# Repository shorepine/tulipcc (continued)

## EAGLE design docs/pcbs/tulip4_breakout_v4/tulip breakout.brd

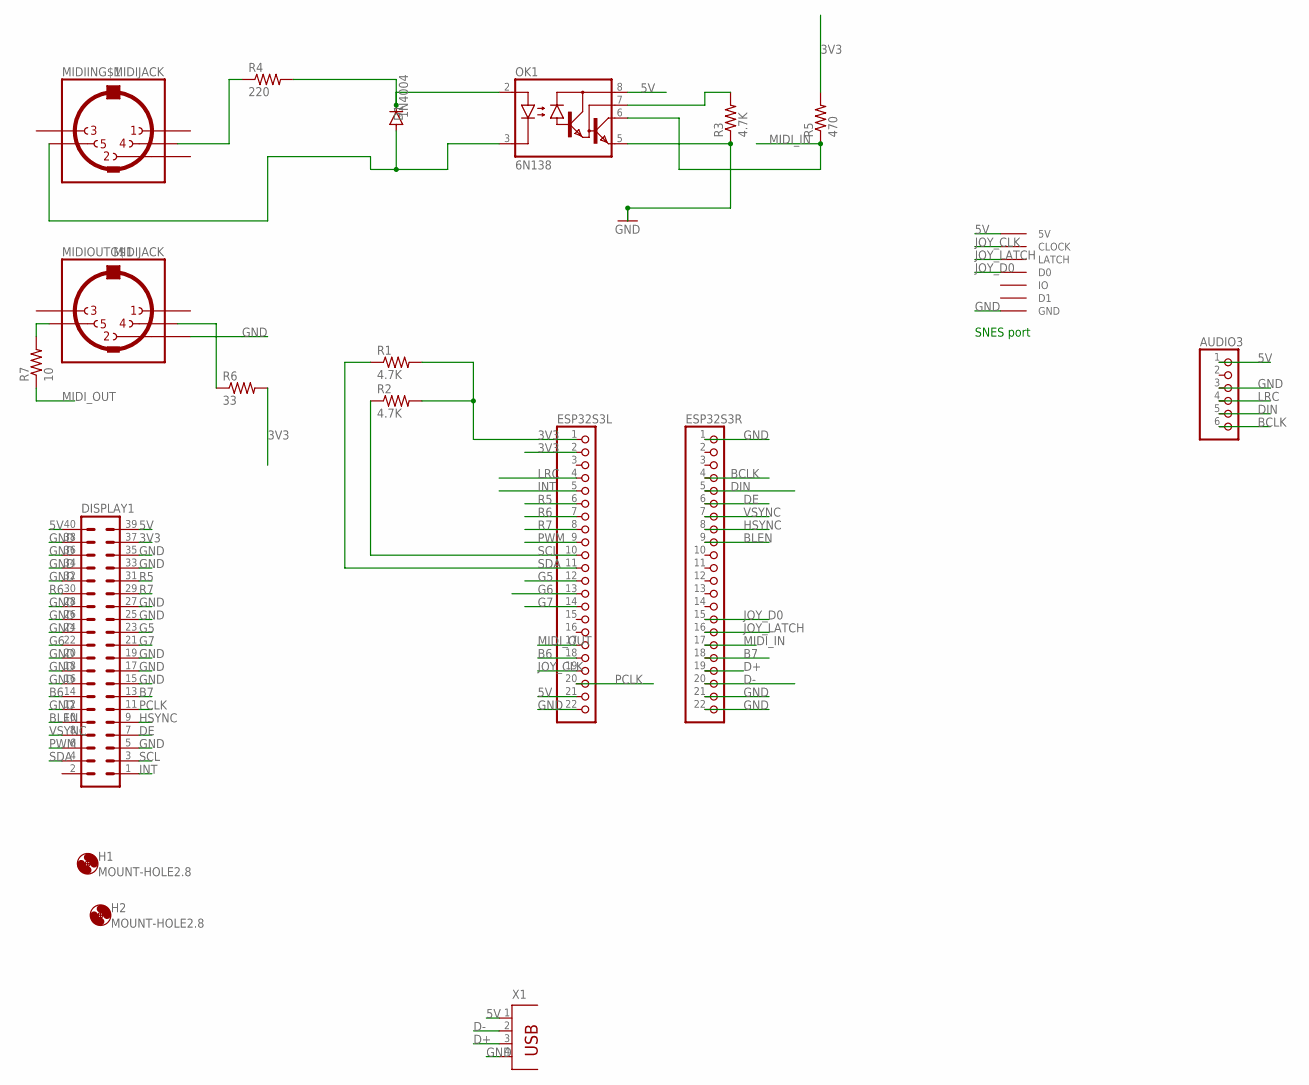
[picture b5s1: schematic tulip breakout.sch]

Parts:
AUDIO3: PINHD-1X6; 1X06
D1: 1N4004; DO41-10
DISPLAY1: MA20-2
ESP32S3L, ESP32S3R: PINHD-1X22; 1X22
H1, H2: MOUNT-HOLE2.8; 2,8
MIDIIN: MIDIJACK; CP-2350
MIDIOUT: MIDIJACK; CP-2350
OK1: 6N138; DIL08
R1, R2, R3: 4.7K; 0207/12
R4: 220; 0207/12
R5: 470; 0207/12
R6: 33; 0207/12
R7: 10; 0207/12
U$2: SNESCONN
X1: PN87520

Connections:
3V3: DISPLAY1.37, ESP32S3L.1, ESP32S3L.2, R1.2, R2.2, R5.2, R6.2
5V: AUDIO3.1, DISPLAY1.39, DISPLAY1.40, ESP32S3L.21, OK1.8 (VCC), U$2.5V, X1.1
B6: DISPLAY1.14, ESP32S3L.18
B7: DISPLAY1.13, ESP32S3R.18
BCLK: AUDIO3.6, ESP32S3R.4
BLEN: DISPLAY1.10, ESP32S3R.9
D+: ESP32S3R.19, X1.3
D-: ESP32S3R.20, X1.2
DE: DISPLAY1.7, ESP32S3R.6
DIN: AUDIO3.5, ESP32S3R.5
G5: DISPLAY1.23, ESP32S3L.12
G6: DISPLAY1.22, ESP32S3L.13
G7: DISPLAY1.21, ESP32S3L.14
GND: AUDIO3.3, DISPLAY1.5, DISPLAY1.12, DISPLAY1.15, DISPLAY1.16, DISPLAY1.17, DISPLAY1.18, DISPLAY1.19, DISPLAY1.20, DISPLAY1.24, DISPLAY1.25, DISPLAY1.26, DISPLAY1.27, DISPLAY1.28, DISPLAY1.32, DISPLAY1.33, DISPLAY1.34, DISPLAY1.35, DISPLAY1.36, DISPLAY1.38, ESP32S3L.22, ESP32S3R.1, ESP32S3R.21, ESP32S3R.22, MIDIOUT.2, OK1.5 (GND), R3.1, U$2.GND, X1.4
HSYNC: DISPLAY1.9, ESP32S3R.8
INT: DISPLAY1.1, ESP32S3L.5
JOY_CLK: ESP32S3L.19, U$2.CLOCK
JOY_D0: ESP32S3R.15, U$2.D0
JOY_LATCH: ESP32S3R.16, U$2.LATCH
LRC: AUDIO3.4, ESP32S3L.4
MIDI_IN: ESP32S3R.17, OK1.6 (VO), R5.1
MIDI_OUT: ESP32S3L.17, R7.1
unnamed: MIDIIN.4, R4.1
unnamed: D1.C, OK1.2 (A), R4.2
unnamed: D1.A, MIDIIN.5, OK1.3 (C)
unnamed: OK1.7 (VB), R3.2
unnamed: MIDIOUT.5, R7.2
unnamed: MIDIOUT.4, R6.1
PCLK: DISPLAY1.11, ESP32S3L.20
PWM: DISPLAY1.6, ESP32S3L.9
R5: DISPLAY1.31, ESP32S3L.6
R6: DISPLAY1.30, ESP32S3L.7
R7: DISPLAY1.29, ESP32S3L.8
SCL: DISPLAY1.3, ESP32S3L.10, R2.1
SDA: DISPLAY1.4, ESP32S3L.11, R1.1
VSYNC: DISPLAY1.8, ESP32S3R.7

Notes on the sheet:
SNES port

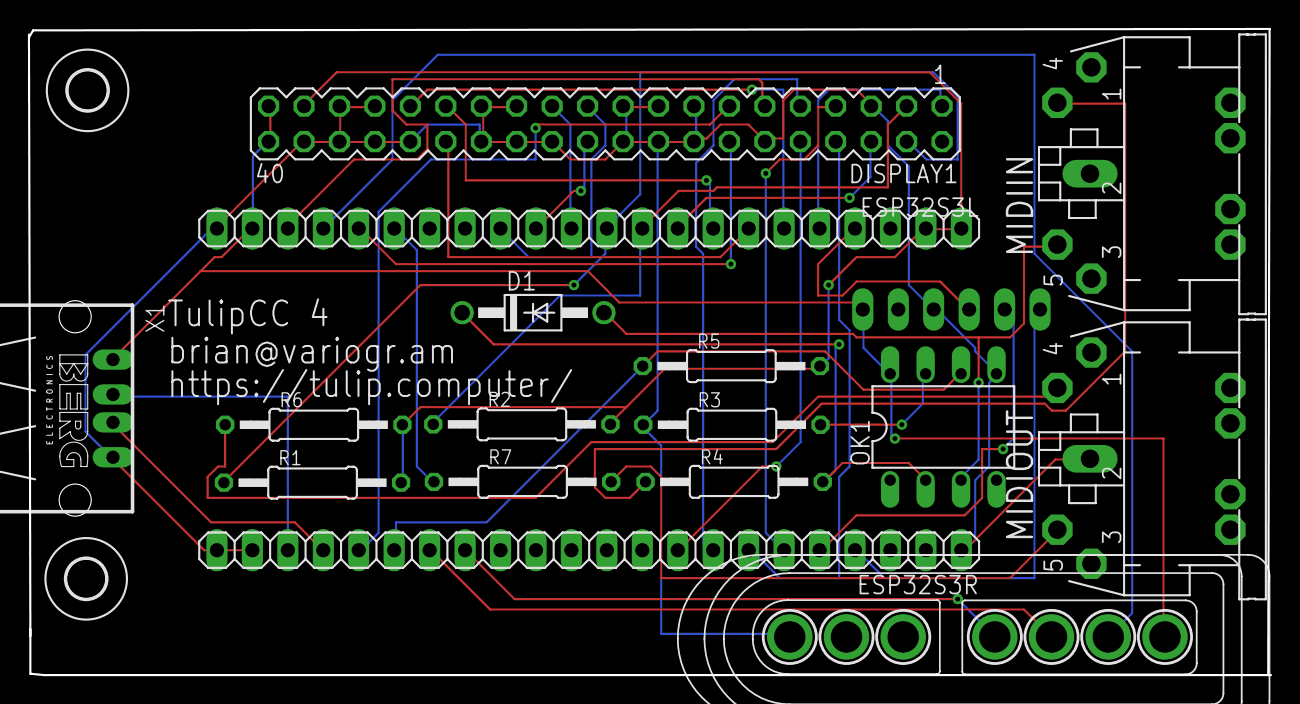
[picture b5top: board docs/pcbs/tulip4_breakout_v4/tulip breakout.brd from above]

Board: 2 copper layers, 89.0 x 46.3 mm, 19 parts (1 on the bottom side), 36 nets.

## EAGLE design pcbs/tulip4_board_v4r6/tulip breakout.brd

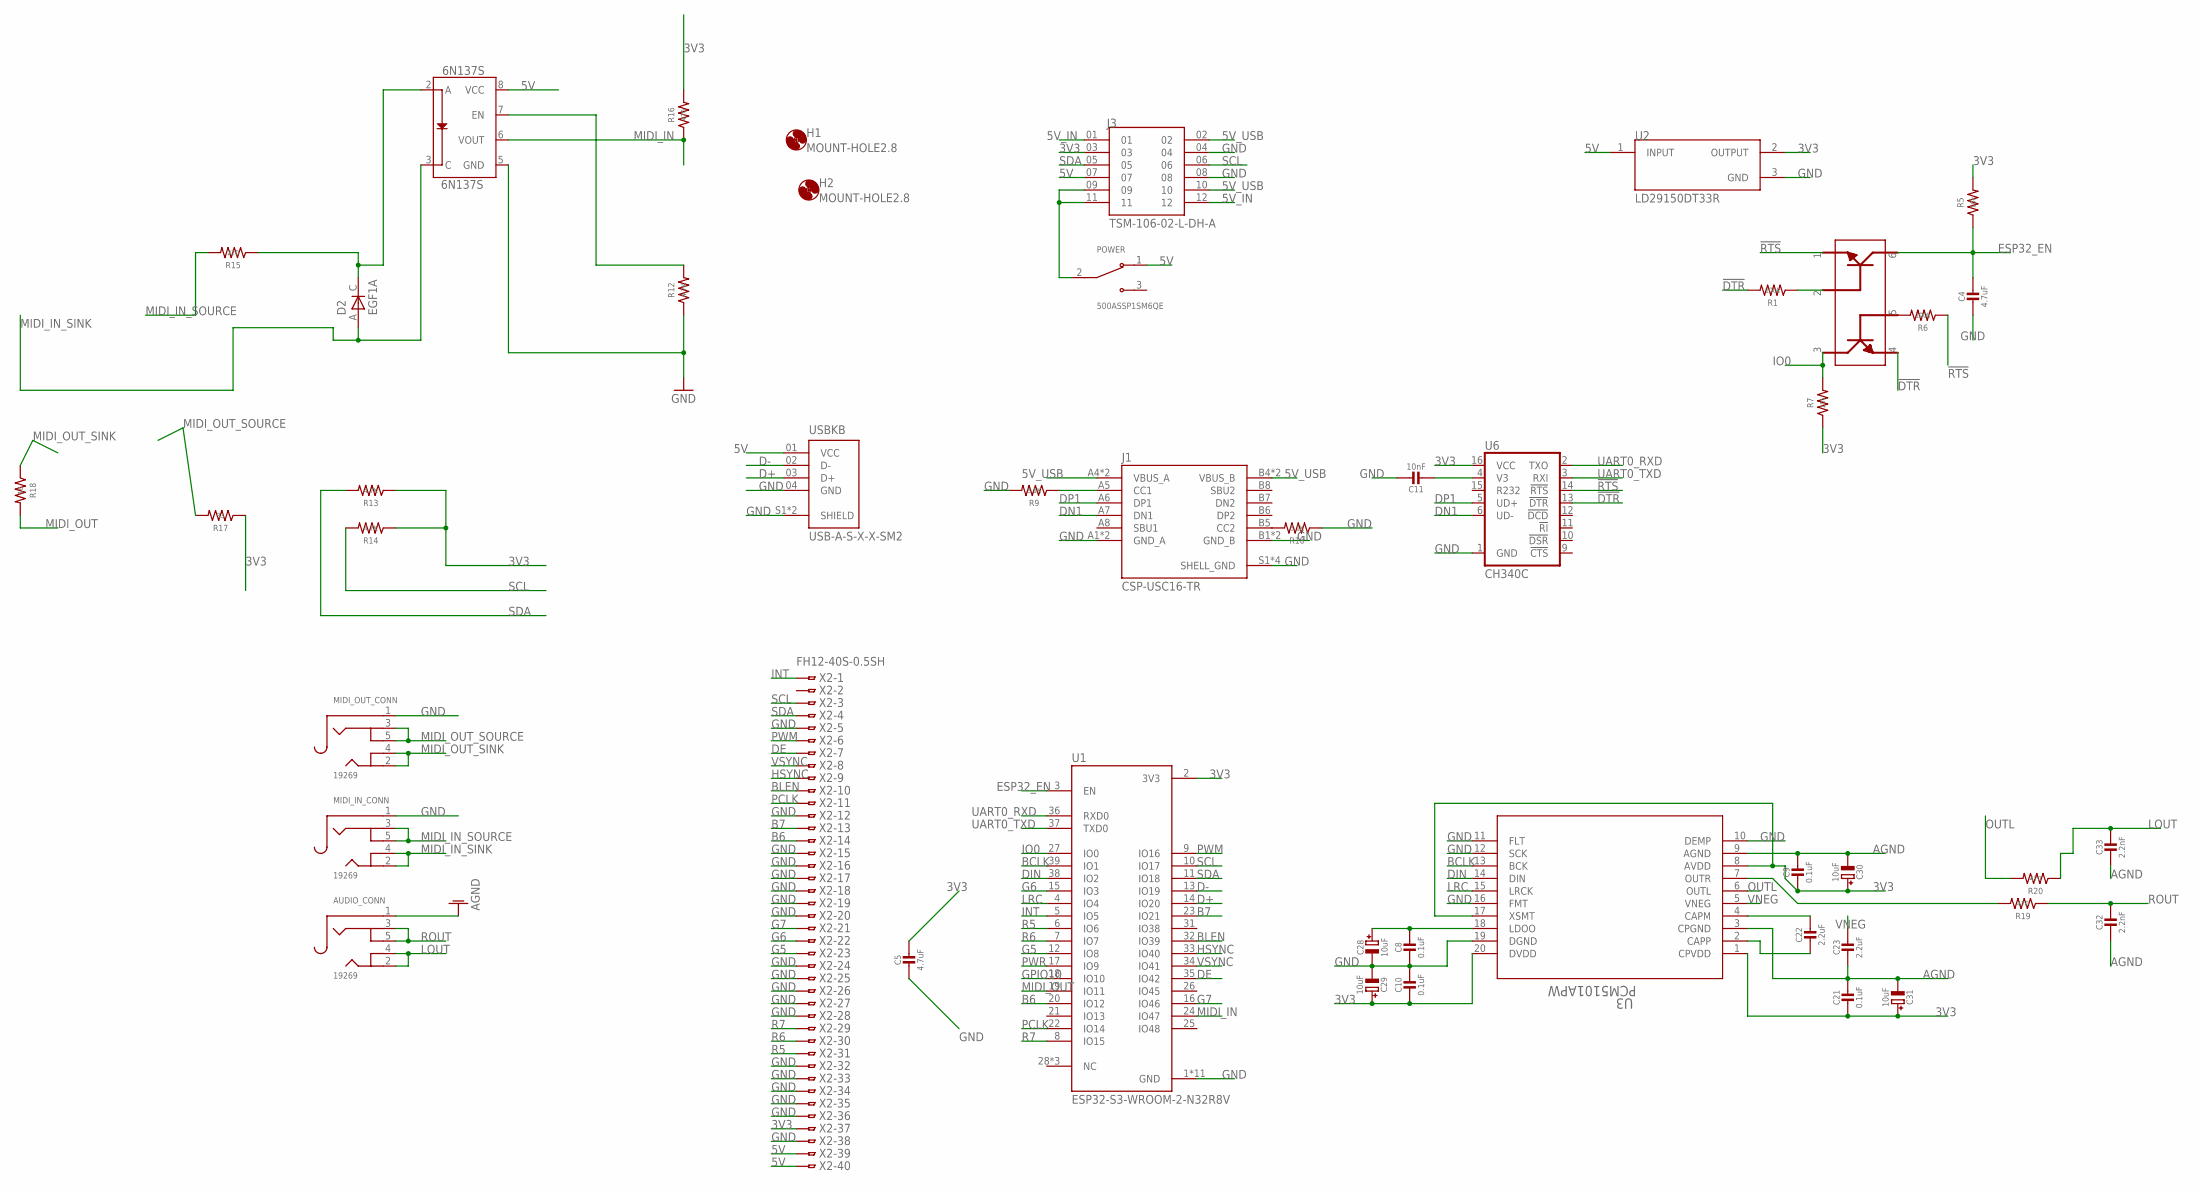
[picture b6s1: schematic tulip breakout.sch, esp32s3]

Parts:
6N137S: 6N137S; 8-SMD
AUDIO_CONN: 19269; 4UCONN_19269
C4, C5: 4.7uF; 0805-NO
C8, C9, C10, C21: 0.1uF; 0805-NO
C11: 10nF; 0805-NO
C22, C23: 2.2uF; 0805-NO
C28, C29, C30, C31: 10uF; PANASONIC_C
C32, C33: 2.2nF; 0805-NO
D2: EGF1A; DIOM449X264X300L114X135N
H1, H2: MOUNT-HOLE2.8; 2,8
J1: CSP-USC16-TR; VALCON_CSP-USC16-TR
J3: TSM-106-02-L-DH-A; SAMTEC_TSM-106-02-L-DH-A
MIDI_IN_CONN: 19269; 4UCONN_19269
MIDI_OUT_CONN: 19269; 4UCONN_19269
POWER: 500ASSP1SM6QE; SW_500ASSP1SM6QE
R1, R6: 100k; R0805
R5, R7: 10k; R0805
R9, R10: 5.1K; R0805
R12, R13, R14: 4.7K; R0805
R15: 220; R0805
R16, R19, R20: 470; R0805
R17: 33; R0805
R18: 10; R0805
RESET: MBT3904DW1T1G; SOT236
U1: ESP32-S3-WROOM-2-N32R8V; XCVR_ESP32-S3-WROOM-2-N32R8V
U2: LD29150DT33R; DPAK456P972X240-3N
U3: PCM5101APW; PW20_TEX
U6: CH340C; SO016
USBKB: USB-A-S-X-X-SM2; SAMTEC_USB-A-S-X-X-SM2
X2: FH12-40S-0.5SH

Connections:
5V: 6N137S.8 (VCC), J3.07, POWER.1 (NC), U2.1 (INPUT), USBKB.01 (VCC), X2.39, X2.40
5V_IN: J3.01, J3.12
!DTR: R1.2, RESET.4, U6.13 (!DTR)
!RTS: R6.1, RESET.1, U6.14 (!RTS)
AGND: AUDIO_CONN.1, C9.1, C21.1, C23.2, C30.-, C31.-, C32.2, C33.2, U3.3 (CPGND), U3.9 (AGND)
B6: U1.20 (IO12), X2.14
B7: U1.23 (IO21), X2.13
BCLK: U1.39 (IO1), U3.13 (BCK)
BLEN: U1.32 (IO39), X2.10
D+: U1.14 (IO20), USBKB.03 (D+)
D-: U1.13 (IO19), USBKB.02 (D-)
DE: U1.35 (IO42), X2.7
DIN: U1.38 (IO2), U3.14 (DIN)
DN1: J1.A7 (DN1), U6.6 (UD-)
DP1: J1.A6 (DP1), U6.5 (UD+)
ESP32_EN: C4.1, R5.1, RESET.6, U1.3 (EN)
G5: U1.12 (IO8), X2.23
G6: U1.15 (IO3), X2.22
G7: U1.16 (IO46), X2.21
GND: 6N137S.5 (GND), C4.2, C5.2, C8.2, C10.1, C11.1, C28.-, C29.-, J1.A1 (GND_A), J1.A12 (GND_A), J1.B1 (GND_B), J1.B12 (GND_B), J1.S1 (SHELL_GND), J1.S2 (SHELL_GND), J1.S3 (SHELL_GND), J1.S4 (SHELL_GND), J3.04, J3.08, MIDI_IN_CONN.1, MIDI_OUT_CONN.1, R9.2, R10.1, R12.1, U1.1 (GND), U1.40 (GND), U1.41_1 (GND), U1.41_2 (GND), U1.41_3 (GND), U1.41_4 (GND), U1.41_5 (GND), U1.41_6 (GND), U1.41_7 (GND), U1.41_8 (GND), U1.41_9 (GND), U2.3 (GND), U3.10 (DEMP), U3.11 (FLT), U3.12 (SCK), U3.16 (FMT), U3.19 (DGND), U6.1 (GND), USBKB.04 (GND), USBKB.S1 (SHIELD), USBKB.S2 (SHIELD), X2.5, X2.12, X2.15, X2.16, X2.17, X2.18, X2.19, X2.20, X2.24, X2.25, X2.26, X2.27, X2.28, X2.32, X2.33, X2.34, X2.35, X2.36, X2.38
GPIO10: U1.18 (IO10)
HSYNC: U1.33 (IO40), X2.9
INT: U1.5 (IO5), X2.1
IO0: R7.2, RESET.3, U1.27 (IO0)
LOUT: AUDIO_CONN.2, AUDIO_CONN.4, C33.1, R20.1
LRC: U1.4 (IO4), U3.15 (LRCK)
MIDI_IN: 6N137S.6 (VOUT), R16.1, U1.24 (IO47)
MIDI_IN_SINK: 6N137S.3 (C), D2.A, MIDI_IN_CONN.2, MIDI_IN_CONN.4
MIDI_IN_SOURCE: MIDI_IN_CONN.3, MIDI_IN_CONN.5, R15.2
MIDI_OUT: R18.2, U1.19 (IO11)
MIDI_OUT_SINK: MIDI_OUT_CONN.2, MIDI_OUT_CONN.4, R18.1
MIDI_OUT_SOURCE: MIDI_OUT_CONN.3, MIDI_OUT_CONN.5, R17.2
unnamed: R1.1, RESET.2
unnamed: R6.2, RESET.5
unnamed: J1.B5 (CC2), R10.2
unnamed: C8.1, C28.+, U3.18 (LDOO)
unnamed: R19.2, U3.7 (OUTR)
unnamed: J3.09, J3.11, POWER.2 (COM)
unnamed: C22.1, U3.4 (CAPM)
unnamed: C22.2, U3.2 (CAPP)
unnamed: 6N137S.2 (A), D2.C, R15.1
unnamed: 6N137S.7 (EN), R12.2
unnamed: C11.2, U6.4 (V3)
unnamed: J1.A5 (CC1), R9.1
OUTL: R20.2, U3.6 (OUTL)
PCLK: U1.22 (IO14), X2.11
PWM: U1.9 (IO16), X2.6
PWR: U1.17 (IO9)
R5: U1.6 (IO6), X2.31
R6: U1.7 (IO7), X2.30
R7: U1.8 (IO15), X2.29
ROUT: AUDIO_CONN.3, AUDIO_CONN.5, C32.1, R19.1
SCL: J3.06, R14.2, U1.10 (IO17), X2.3
SDA: J3.05, R13.2, U1.11 (IO18), X2.4
UART0_RXD: U1.36 (RXD0), U6.2 (TXO)
UART0_TXD: U1.37 (TXD0), U6.3 (RXI)
VNEG: C23.1, U3.5 (VNEG)
VSYNC: U1.34 (IO41), X2.8

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
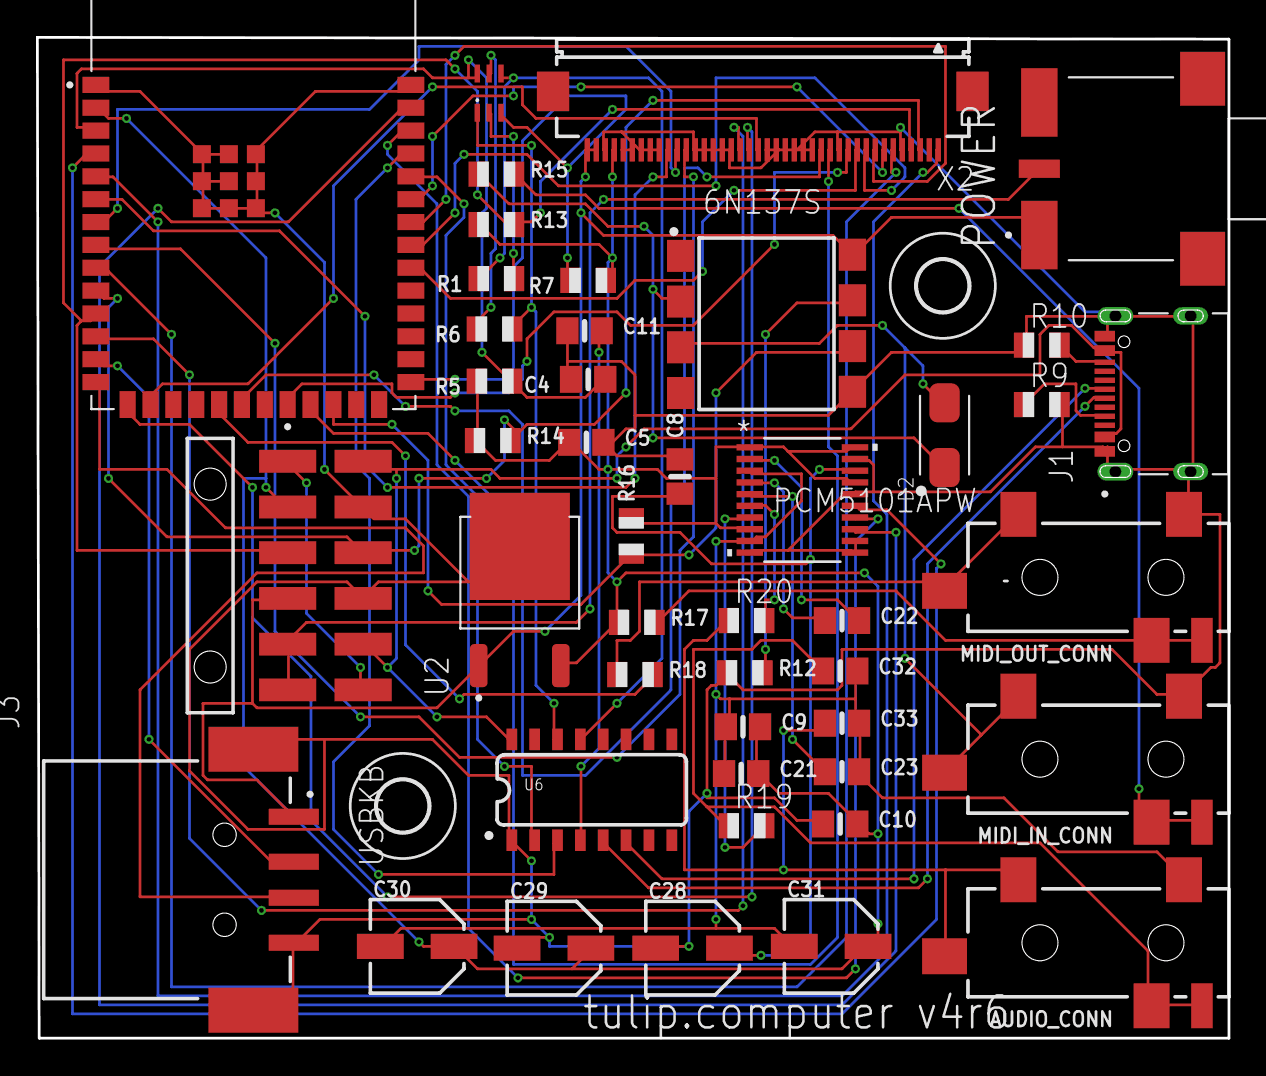
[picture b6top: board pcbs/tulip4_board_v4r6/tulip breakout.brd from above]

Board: 2 copper layers, 66.2 x 55.6 mm, 47 parts (0 on the bottom side), 58 nets.

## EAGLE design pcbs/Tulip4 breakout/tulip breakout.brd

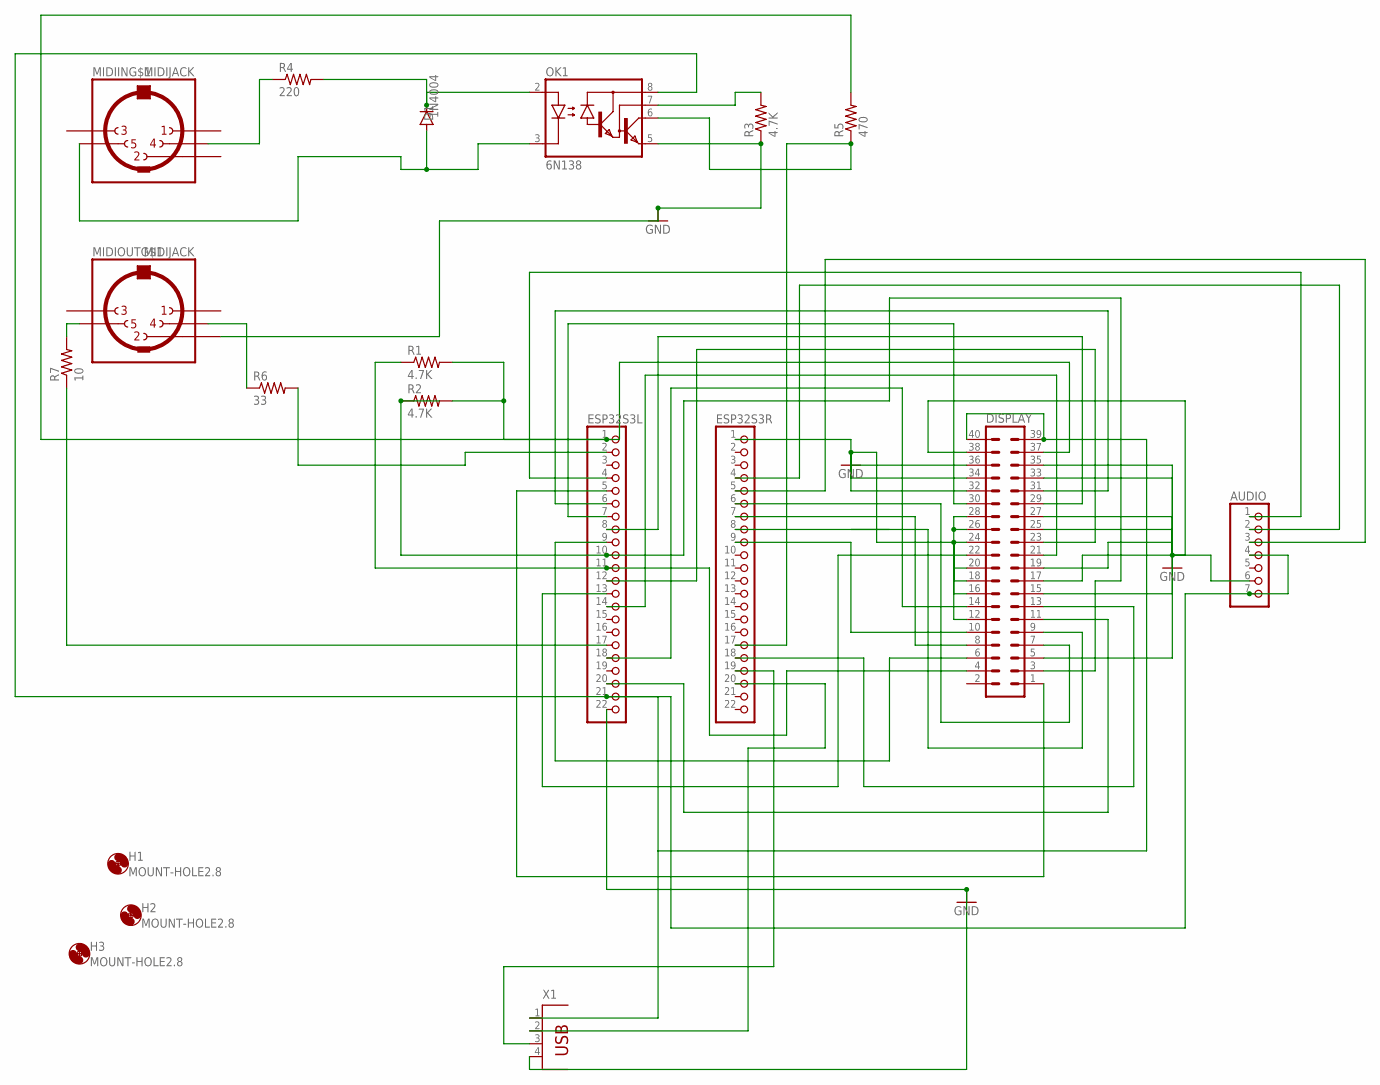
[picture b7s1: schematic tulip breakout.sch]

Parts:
AUDIO: PINHD-1X7; 1X07
D1: 1N4004; DO41-10
DISPLAY: MA20-2
ESP32S3L, ESP32S3R: PINHD-1X22; 1X22
H1, H2, H3: MOUNT-HOLE2.8; 2,8
MIDIIN: MIDIJACK; CP-2350
MIDIOUT: MIDIJACK; CP-2350
OK1: 6N138; DIL08
R1, R2, R3: 4.7K; 0204/7
R4: 220; 0204/7
R5: 470; 0204/7
R6: 33; 0204/7
R7: 10; 0204/7
X1: PN87520

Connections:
GND: AUDIO.6, DISPLAY.5, DISPLAY.12, DISPLAY.15, DISPLAY.16, DISPLAY.17, DISPLAY.18, DISPLAY.19, DISPLAY.20, DISPLAY.24, DISPLAY.25, DISPLAY.26, DISPLAY.27, DISPLAY.28, DISPLAY.32, DISPLAY.33, DISPLAY.34, DISPLAY.35, DISPLAY.36, DISPLAY.38, ESP32S3L.22, ESP32S3R.1, MIDIOUT.2, OK1.5 (GND), R3.1, X1.4
unnamed: DISPLAY.6, ESP32S3L.9
unnamed: DISPLAY.7, ESP32S3R.6
unnamed: DISPLAY.8, ESP32S3R.7
unnamed: DISPLAY.9, ESP32S3R.8
unnamed: DISPLAY.10, ESP32S3R.9
unnamed: DISPLAY.11, ESP32S3L.20
unnamed: DISPLAY.13, ESP32S3R.18
unnamed: DISPLAY.14, ESP32S3L.18
unnamed: AUDIO.4, AUDIO.7, DISPLAY.39, DISPLAY.40, ESP32S3L.21, OK1.8 (VCC), X1.1
unnamed: DISPLAY.21, ESP32S3L.14
unnamed: DISPLAY.22, ESP32S3L.13
unnamed: DISPLAY.23, ESP32S3L.12
unnamed: DISPLAY.29, ESP32S3L.8
unnamed: DISPLAY.30, ESP32S3L.7
unnamed: DISPLAY.31, ESP32S3L.6
unnamed: DISPLAY.37, ESP32S3L.1, R1.2, R2.2, R5.2
unnamed: DISPLAY.4, ESP32S3L.11, R1.1
unnamed: ESP32S3R.17, OK1.6 (VO), R5.1
unnamed: DISPLAY.1, ESP32S3L.5
unnamed: AUDIO.1, ESP32S3L.4
unnamed: AUDIO.2, ESP32S3R.4
unnamed: AUDIO.3, ESP32S3R.5
unnamed: ESP32S3R.20, X1.2
unnamed: ESP32S3R.19, X1.3
unnamed: DISPLAY.3, ESP32S3L.10, R2.1
unnamed: ESP32S3L.17, R7.1
unnamed: MIDIIN.4, R4.1
unnamed: D1.C, OK1.2 (A), R4.2
unnamed: D1.A, MIDIIN.5, OK1.3 (C)
unnamed: OK1.7 (VB), R3.2
unnamed: MIDIOUT.5, R7.2
unnamed: MIDIOUT.4, R6.1
unnamed: ESP32S3L.2, R6.2

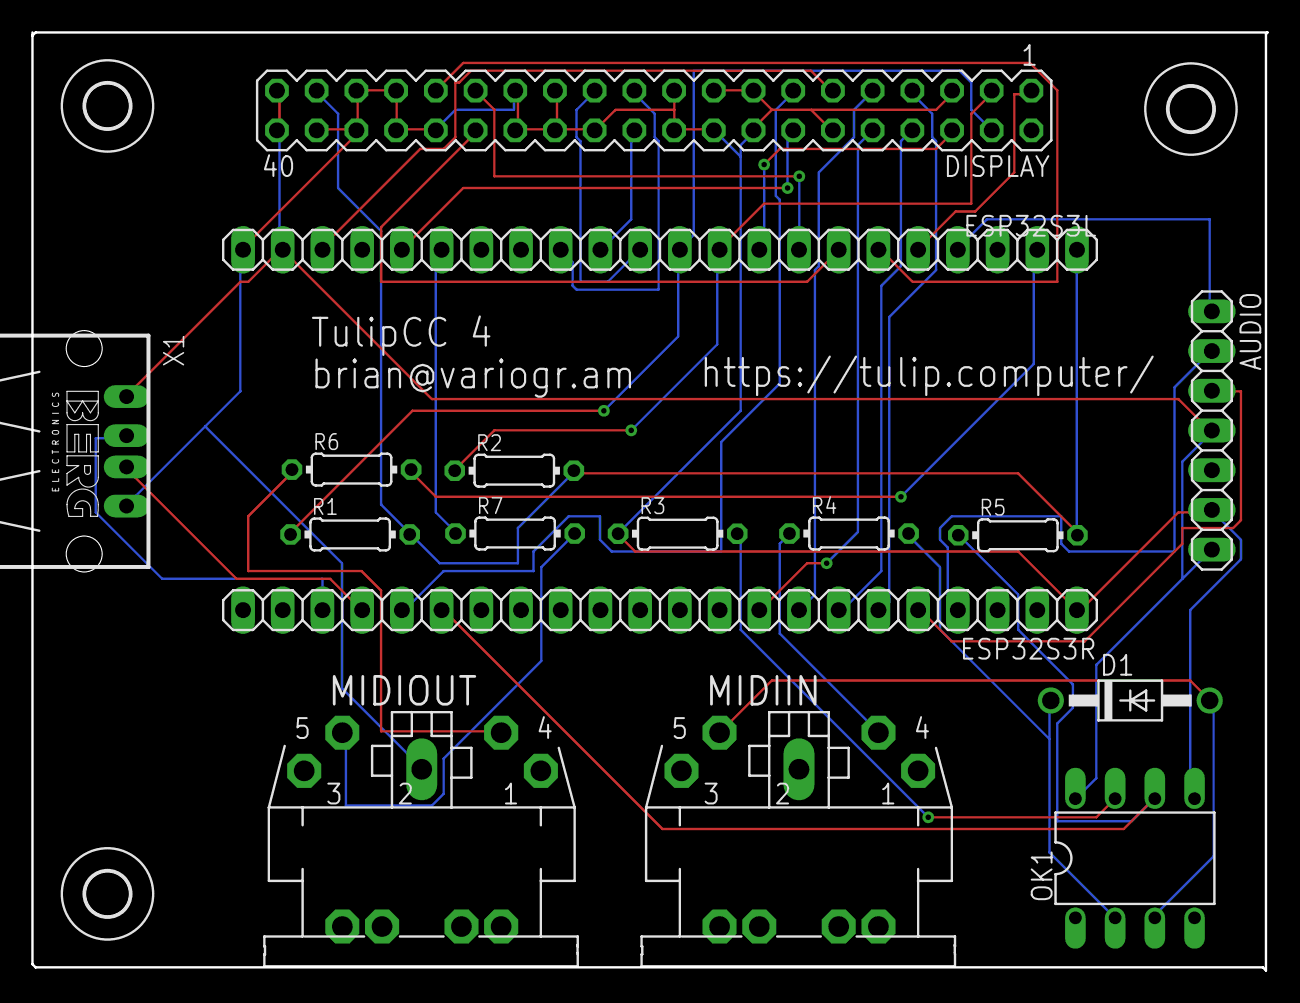
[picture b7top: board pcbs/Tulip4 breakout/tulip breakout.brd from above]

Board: 2 copper layers, 79.0 x 60.0 mm, 19 parts (0 on the bottom side), 34 nets.

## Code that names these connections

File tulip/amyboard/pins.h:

// pins.h
// pins (and other MCU constants) 

#define SPI_LL_DATA_MAX_BIT_LEN (1 << 18)

#define I2C_NUM I2C_NUM_0
#define I2C_CLK_FREQ 400000
#define ESP_INTR_FLAG_DEFAULT 0

// stuff in the eagle
#define CONFIG_I2S_MCLK  3
#define CONFIG_I2S_BCLK  8
#define CONFIG_I2S_LRCLK 2
#define CONFIG_I2S_DOUT 6 // data going to the codec, eg DAC data, also called AMYOUT
#define I2C_FOLLOWER_SCL 5
#define I2C_FOLLOWER_SDA 4 
#define I2C_MASTER_SCL 18
#define I2C_MASTER_SDA 17
#define CONFIG_I2S_DIN 9 // data coming from the codec, eg ADC  data, also called AMYIN

#define MIDI_OUT_PIN_A 14
#define MIDI_OUT_PIN_B 15

#define MIDI_IN_PIN 21
#define MPIO_C0 7

#define SPI0_CS0 10
#define SPI0_MOSI 11
#define SPI0_SCK 12
#define SPI0_MISO 13

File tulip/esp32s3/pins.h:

// pins.h
// pins (and other MCU constants) for all Tulip variants

#define BK_LIGHT_ON_LEVEL  1
#ifndef DEFAULT_BRIGHTNESS
#define DEFAULT_BRIGHTNESS 9 // 9 is max, 1 is min
#endif
#define BK_LIGHT_OFF_LEVEL !BK_LIGHT_ON_LEVEL
#define SPI_LL_DATA_MAX_BIT_LEN (1 << 18)

#ifdef TDECK
#define TDECK_PERI_GPIO 10
#define TDECK_LCD_BK_LIGHT_GPIO  42
#define TDECK_LCD_RST_GPIO       -1
#define TDECK_LCD_CS_GPIO        12
#define TDECK_LCD_DC_GPIO        11
#define TDECK_LCD_PCLK_GPIO      40
#define TDECK_LCD_MOSI_GPIO     41 // MOSI
#define TDECK_LCD_MISO_GPIO     38 // MISO
#define TDECK_LCD_PIXEL_CLOCK_HZ (80 * 1000 * 1000)
#define TDECK_SPI_HOST_ID SPI2_HOST
#define TDECK_POWERON       10
#define TDECK_I2C_SDA       18
#define TDECK_I2C_SCL       8
#define LILYGO_KB_SLAVE_ADDRESS     0x55
#define TDECK_TOUCH_ADDR_0 0x14
#define TDECK_TOUCH_ADDR_1 0x5D
#define TDECK_TRACKBALL_UP 3
#define TDECK_TRACKBALL_DOWN 15
#define TDECK_TRACKBALL_LEFT 1
#define TDECK_TRACKBALL_RIGHT 2
#define TDECK_TRACKBALL_CLICK 0
#define TOUCH_INT 16
#define I2C_SCL 8
#define I2C_SDA 18
#define I2C_NUM I2C_NUM_0
#define I2C_CLK_FREQ 400000
#define TOUCH_RST -1
#define ESP_INTR_FLAG_DEFAULT 0
#define CONFIG_I2S_LRCLK 5
#define CONFIG_I2S_BCLK 7
#define CONFIG_I2S_DOUT 6
#define CONFIG_I2S_DIN -1
#define CONFIG_I2S_NUM 0
#define MIDI_OUT_PIN UART_PIN_NO_CHANGE
#define MIDI_IN_PIN UART_PIN_NO_CHANGE 
#endif

// Tulip4R10, V0, MaTouch7
#ifdef MAKERFABS 
#define I2C_SDA 17
#define I2C_SCL 18
#define TOUCH_INT -1
#define I2C_NUM I2C_NUM_0
#define I2C_CLK_FREQ 100000
#define DEFAULT_BRIGHTNESS 9 // 9 is max, 1 is min
#define HSYNC_BACK_PORCH 16
#define HSYNC_FRONT_PORCH 210
#define HSYNC_PULSE_WIDTH 30
#define VSYNC_BACK_PORCH 10
#define VSYNC_FRONT_PORCH 22
#define VSYNC_PULSE_WIDTH 13
#define PIN_NUM_HSYNC          39
#define PIN_NUM_VSYNC          41
#define PIN_NUM_DE             40
#define PIN_NUM_PCLK           42 

#ifdef MATOUCH7
#define TOUCH_RST 38
#define PIN_NUM_BK_PWM 10
#define PIN_R7 14
#define PIN_R6 21
#define PIN_R5 47
#define PIN_R4 48
#define PIN_R3 45
#define PIN_G7 4
#define PIN_G6 16
#define PIN_G5 15
#define PIN_G4 7
#define PIN_G3 6
#define PIN_G2 5
#define PIN_B7 1
#define PIN_B6 9
#define PIN_B5 46
#define PIN_B4 3
#define PIN_B3 8
#define ESP_INTR_FLAG_DEFAULT 0

// This assumes you've used a SD card adapter to get I2s audio 
#define CONFIG_I2S_LRCLK 13 //2
#define CONFIG_I2S_BCLK 12 //20 
#define CONFIG_I2S_DOUT 11 //19
#define CONFIG_I2S_DIN -1
#define CONFIG_I2S_NUM 0 

// No MIDI on Matouch7
#define MIDI_OUT_PIN UART_PIN_NO_CHANGE
#define MIDI_IN_PIN UART_PIN_NO_CHANGE

#elif defined TULIP4_R11
#define TOUCH_RST 48 
#define PIN_NUM_BK_PWM 47
#define PIN_R7 14
#define PIN_R6 21
#define PIN_R5 10
#define PIN_R4 13
#define PIN_R3 45
#define PIN_G7 4
#define PIN_G6 16
#define PIN_G5 15
#define PIN_G4 7
#define PIN_G3 6
#define PIN_G2 -1
#define PIN_B7 1
#define PIN_B6 9
#define PIN_B5 46
#define PIN_B4 38  
#define PIN_B3 -1 
#define ESP_INTR_FLAG_DEFAULT 0
#define CONFIG_I2S_LRCLK 2
#define CONFIG_I2S_BCLK 8 
#define CONFIG_I2S_DOUT 5 
#define CONFIG_I2S_DIN -1 
#define CONFIG_I2S_NUM 0 
#define MIDI_OUT_PIN 11
#define MIDI_IN_PIN 12

#define PIN_NUM_DISP_EN        -1
#endif
#endif // MAKERFABS



#ifdef TULIP_DIY
#define I2C_SCL                     17
#define I2C_SDA                     18
#define TOUCH_INT                   (5)
#define TOUCH_INT_IO_MUX            (PERIPHS_IO_MUX_GPIO5_U)
#define I2C_NUM                     I2C_NUM_0
#define TOUCH_RST                   -1
#define I2C_CLK_FREQ 400000
#define HSYNC_BACK_PORCH 139
#define HSYNC_FRONT_PORCH 140
#define HSYNC_PULSE_WIDTH 20
#define VSYNC_BACK_PORCH 20
#define VSYNC_FRONT_PORCH 12
#define VSYNC_PULSE_WIDTH 20
#define PIN_NUM_BK_LIGHT       39 // was 19, was 14 white
#define PIN_NUM_HSYNC          40
#define PIN_NUM_VSYNC          41
#define PIN_NUM_DE             42
#define PIN_NUM_PCLK           14 // was 38, was 20, was 13 black
#define PIN_NUM_BK_PWM         16

#define PIN_R7 15  
#define PIN_R6 7   
#define PIN_R5 6   
#define PIN_R4 -1 // NC
#define PIN_R3 -1 // NC

#define PIN_G7 46  
#define PIN_G6 3  
#define PIN_G5 8  
#define PIN_G4 -1 // NC
#define PIN_G3 -1 // NC
#define PIN_G2 -1 // NC

#define PIN_B7 21 
#define PIN_B6 12 
#define PIN_B5 -1 // NC
#define PIN_B4 -1 // NC
#define PIN_B3 -1 // NC 

#define PIN_NUM_DISP_EN        -1
#define ESP_INTR_FLAG_DEFAULT 0
#define CONFIG_I2S_LRCLK 4
#define CONFIG_I2S_BCLK 1
#define CONFIG_I2S_DOUT 2
#define CONFIG_I2S_DIN -1
#define CONFIG_I2S_NUM 0 
#define MIDI_OUT_PIN 11
#define MIDI_IN_PIN 47
#endif


#define CONFIG_I2S_MCLK -1
